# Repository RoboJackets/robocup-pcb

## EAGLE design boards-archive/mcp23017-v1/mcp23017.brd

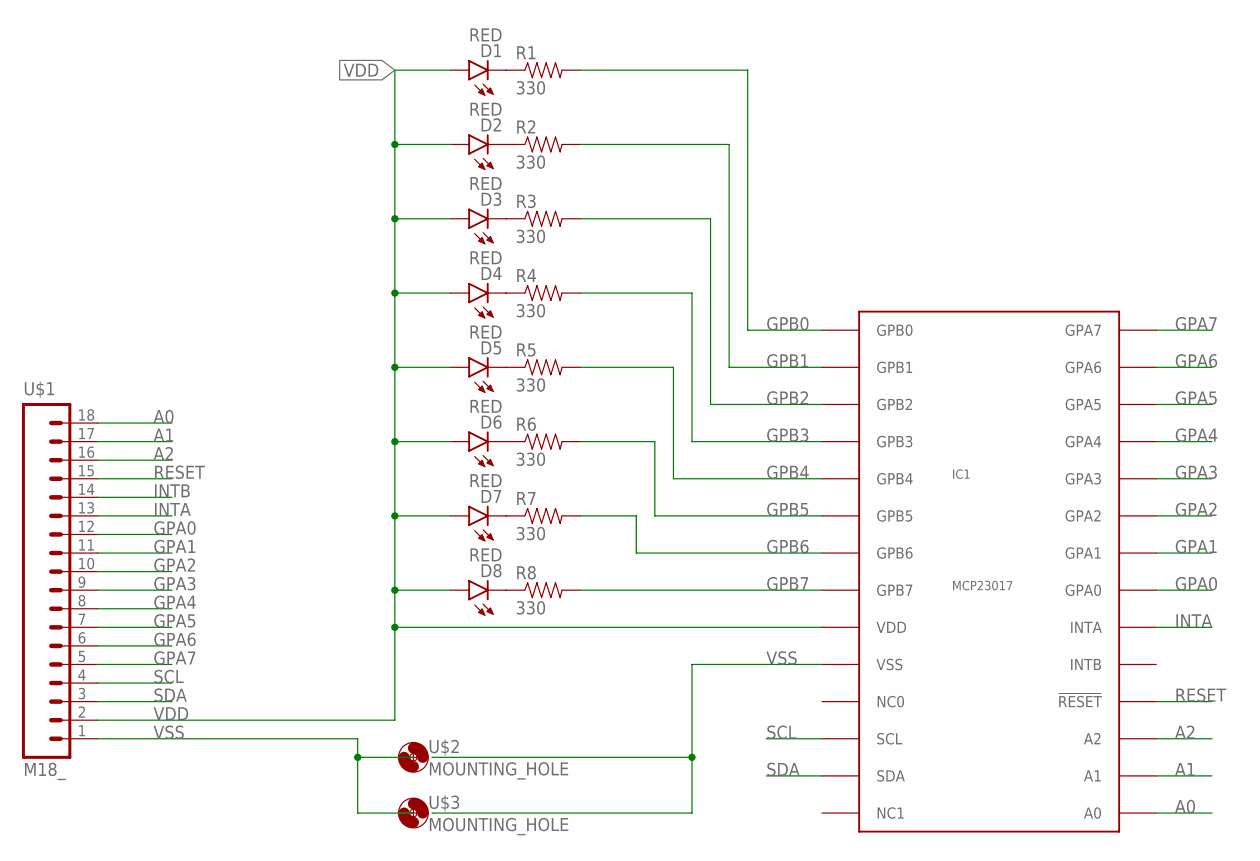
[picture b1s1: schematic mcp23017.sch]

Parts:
D1, D2, D3, D4, D5, D6, D7, D8: RED; LED-0603
IC1: MCP23017; SSOP-28
R1, R2, R3, R4, R5, R6, R7, R8: 330; 0603-RES
U$1: M18_; 1X18
U$2, U$3: MOUNTING_HOLE

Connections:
A0: IC1.15 (A0), U$1.18
A1: IC1.16 (A1), U$1.17
A2: IC1.17 (A2), U$1.16
GPA0: IC1.21 (GPA0), U$1.12
GPA1: IC1.22 (GPA1), U$1.11
GPA2: IC1.23 (GPA2), U$1.10
GPA3: IC1.24 (GPA3), U$1.9
GPA4: IC1.25 (GPA4), U$1.8
GPA5: IC1.26 (GPA5), U$1.7
GPA6: IC1.27 (GPA6), U$1.6
GPA7: IC1.28 (GPA7), U$1.5
GPB0: IC1.1 (GPB0), R1.2
GPB1: IC1.2 (GPB1), R2.2
GPB2: IC1.3 (GPB2), R3.2
GPB3: IC1.4 (GPB3), R4.2
GPB4: IC1.5 (GPB4), R5.2
GPB5: IC1.6 (GPB5), R6.2
GPB6: IC1.7 (GPB6), R7.2
GPB7: IC1.8 (GPB7), R8.2
INTA: IC1.20 (INTA), U$1.13
INTB: U$1.14
unnamed: D1.C, R1.1
unnamed: D2.C, R2.1
unnamed: D3.C, R3.1
unnamed: D4.C, R4.1
unnamed: D5.C, R5.1
unnamed: D6.C, R6.1
unnamed: D7.C, R7.1
unnamed: D8.C, R8.1
RESET: IC1.18 (!RESET!), U$1.15
SCL: IC1.12 (SCL), U$1.4
SDA: IC1.13 (SDA), U$1.3
VDD: D1.A, D2.A, D3.A, D4.A, D5.A, D6.A, D7.A, D8.A, IC1.9 (VDD), U$1.2
VSS: IC1.10 (VSS), U$1.1, U$2.GND, U$3.GND

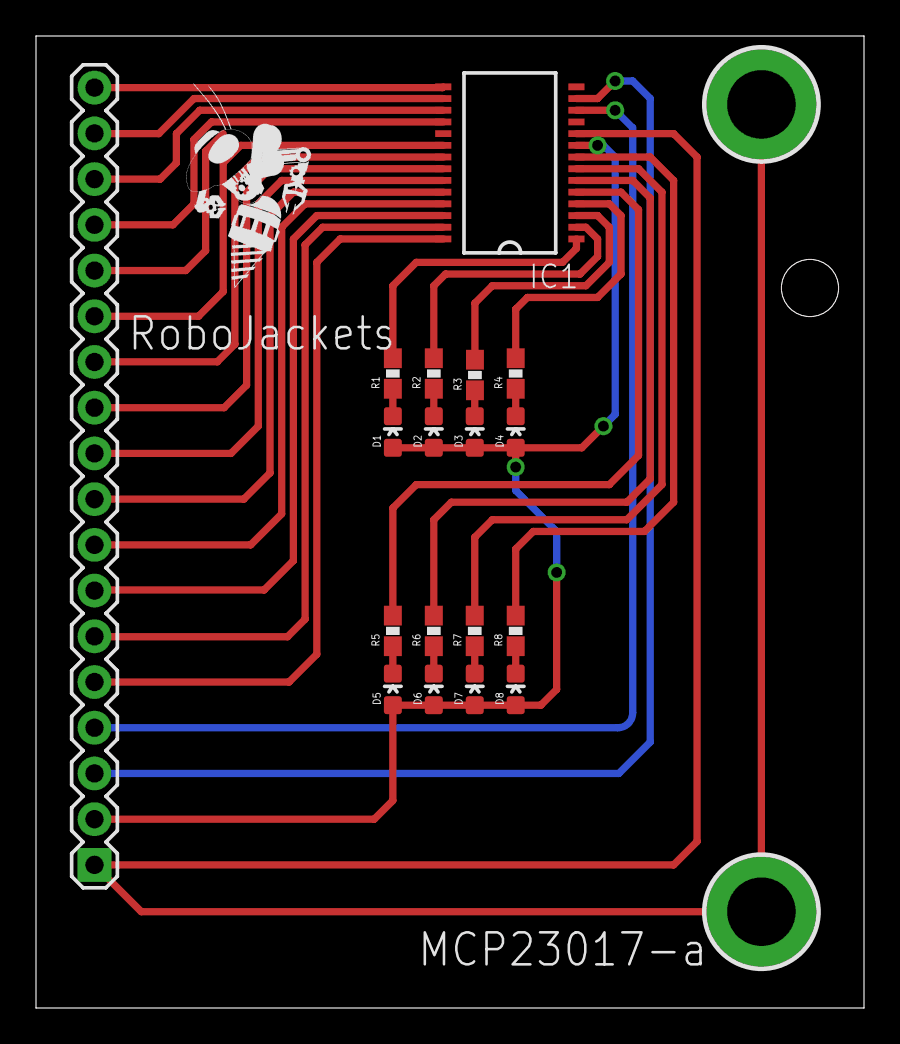
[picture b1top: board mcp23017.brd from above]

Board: 2 copper layers, 46.0 x 54.0 mm, 21 parts (0 on the bottom side), 33 nets.

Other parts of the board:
U$4: ROBOBUZZ_0.6X

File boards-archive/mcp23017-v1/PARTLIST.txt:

Partlist

Exported from mcp23017-v1.brd at 12/27/2014 11:06:29 PM

EAGLE Version 6.5.0 Copyright (c) 1988-2013 CadSoft

Assembly variant: 

Part     Value          Package       Library             Position (mm)         Orientation

D1       RED            LED-0603      SparkFun-LED        (19.825 32)           R0
D2       RED            LED-0603      SparkFun-LED        (22.1 32)             R0
D3       RED            LED-0603      SparkFun-LED        (24.375 32)           R0
D4       RED            LED-0603      SparkFun-LED        (26.65 32)            R0
D5       RED            LED-0603      SparkFun-LED        (19.825 17.7)         R0
D6       RED            LED-0603      SparkFun-LED        (22.1 17.7)           R0
D7       RED            LED-0603      SparkFun-LED        (24.375 17.7)         R0
D8       RED            LED-0603      SparkFun-LED        (26.65 17.7)          R0
IC1      MCP23017       SSOP-28       RoboJackets-ICs     (26.325 46.95)        R180
R1       330            0603-RES      SparkFun-Resistors  (19.825 35.25)        R90
R2       330            0603-RES      SparkFun-Resistors  (22.1 35.25)          R90
R3       330            0603-RES      SparkFun-Resistors  (24.385 35.165)       R90
R4       330            0603-RES      SparkFun-Resistors  (26.65 35.25)         R90
R5       330            0603-RES      SparkFun-Resistors  (19.825 20.95)        R90
R6       330            0603-RES      SparkFun-Resistors  (22.1 20.95)          R90
R7       330            0603-RES      SparkFun-Resistors  (24.375 20.95)        R90
R8       330            0603-RES      SparkFun-Resistors  (26.65 20.95)         R90
U$1      M18_           1X18          SparkFun-Connectors (3.25 7.95)           R90
U$2      MOUNTING_HOLE  MOUNTING_HOLE RoboJackets-Passive (40.3 5.35)           R0
U$3      MOUNTING_HOLE  MOUNTING_HOLE RoboJackets-Passive (40.3 50.2)           R0

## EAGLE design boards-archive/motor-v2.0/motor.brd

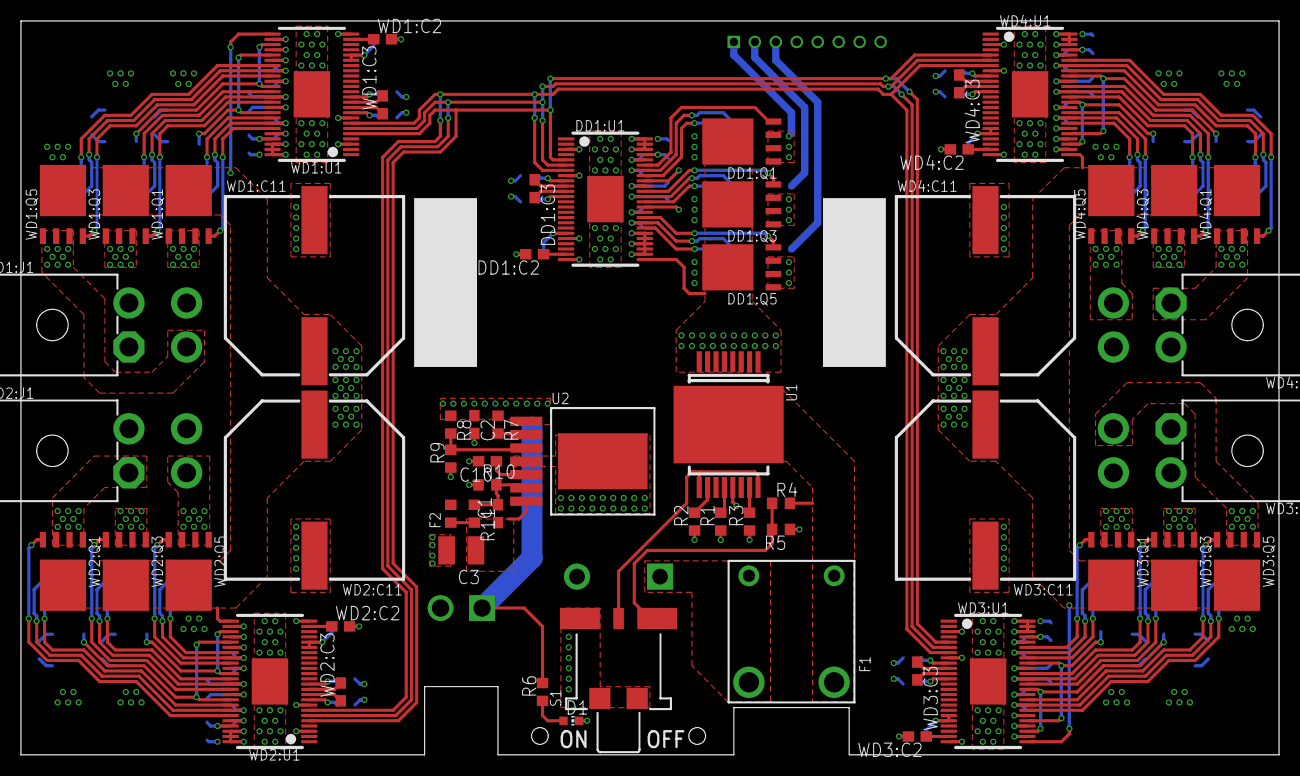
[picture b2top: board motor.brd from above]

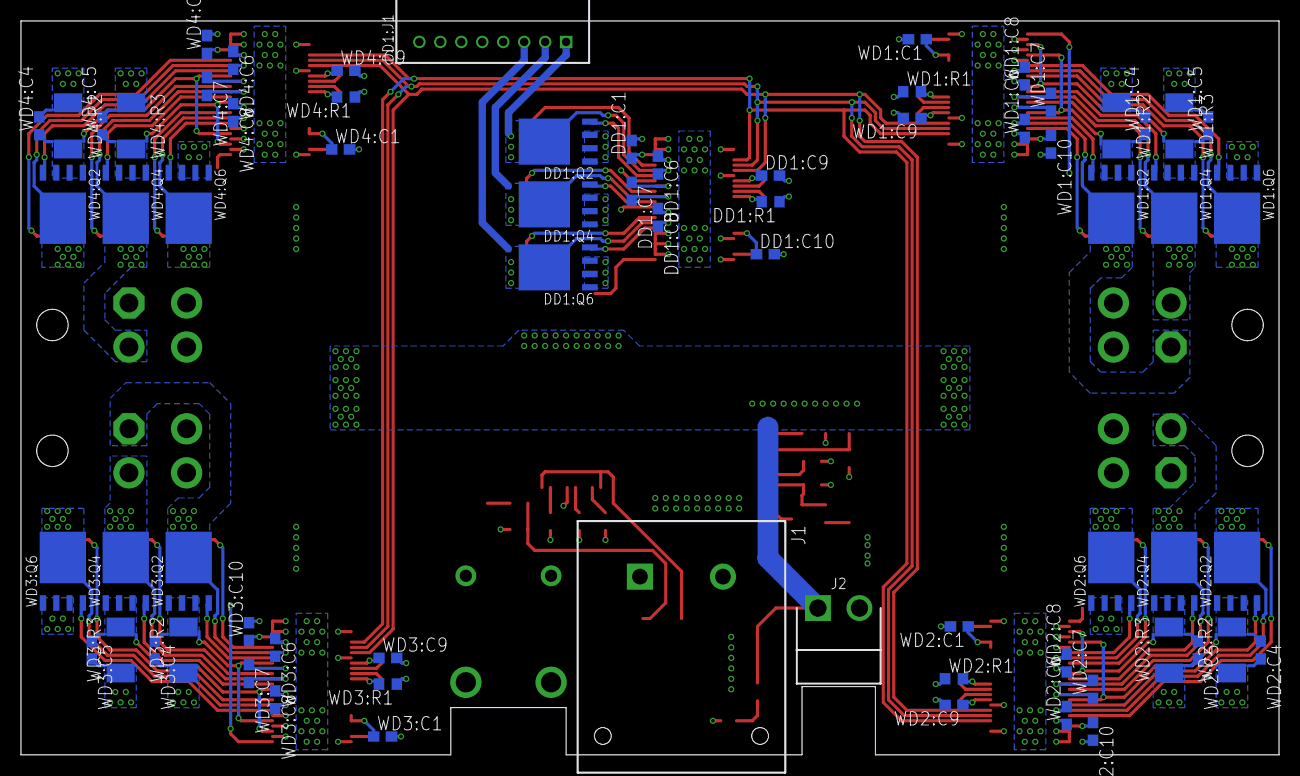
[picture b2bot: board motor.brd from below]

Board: 4 copper layers, 120.0 x 70.0 mm, 128 parts (69 on the bottom side), 112 nets.

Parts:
C1: 0.022uF; C0603
C2: GRM188R6YA106MA73D; C0603
C3: LMK325ABJ107MM-P; C1210
C10: 0.1uF 50V; C0603
D1: Green; CHIP-LED0603
DD1:C1, DD1:C2: 1uF; C0603
DD1:C3: 22000pF 50V; C0603
DD1:C6, DD1:C7, DD1:C8, DD1:C10: 0.1uF 50V; C0603
DD1:C9: 2.2uF 50V; C0603
DD1:J1: 8-PIN_2MM-H; 2MM-8-H
DD1:Q1, DD1:Q2, DD1:Q3, DD1:Q4, DD1:Q5, DD1:Q6: IRFH7545; PQFN_5X6_E
DD1:R1: 10k; R0603
DD1:U1: DRV8303DCA; TSSOP-48_PAD
F1: 30A; FUSEHOLDER_3549_X2
F2: 0603L075SLYR; F0603
J1: DF22-2; DF22-2-H
J2: B2PS-CENTERED-VH(LF)(SN); B2PS-CENTERED
R1: 10k; R0603
R2, R3, R6: 1k; R0603
R4, R8: 270k; R0603
R5, R7, R9: 100k; R0603
R10: 6.49k; R0603
R11: 34k; R0603
S1: 34EWMSP12MRT; 34EWMSP12M6RT
U1: VND5E006ASPTR-E; POWERSO-16
U2: LMZ14201; TO-PMOD-7
WD1:C1, WD1:C2, WD2:C1, WD2:C2, WD3:C1, WD3:C2, WD4:C1, WD4:C2: 1uF; C0603
WD1:C3, WD2:C3, WD3:C3, WD4:C3: 22000pF 50V; C0603
WD1:C4, WD1:C5, WD2:C4, WD2:C5, WD3:C4, WD3:C5, WD4:C4, WD4:C5: 10000pF 50V; C0603
WD1:C6, WD1:C7, WD1:C8, WD1:C10, WD2:C6, WD2:C7, WD2:C8, WD2:C10, WD3:C6, WD3:C7, WD3:C8, WD3:C10, WD4:C6, WD4:C7, WD4:C8, WD4:C10: 0.1uF 50V; C0603
WD1:C9, WD2:C9, WD3:C9, WD4:C9: 2.2uF 50V; C0603
WD1:C11, WD2:C11, WD3:C11, WD4:C11: EEE-FK1H102AM; PANASONIC_J16
WD1:J1, WD2:J1, WD3:J1, WD4:J1: MINIFITJR_HDR_2X2; 0039301040
WD1:Q1, WD1:Q2, WD1:Q3, WD1:Q4, WD1:Q5, WD1:Q6, WD2:Q1, WD2:Q2, WD2:Q3, WD2:Q4, WD2:Q5, WD2:Q6, WD3:Q1, WD3:Q2, WD3:Q3, WD3:Q4, WD3:Q5, WD3:Q6, WD4:Q1, WD4:Q2, WD4:Q3, WD4:Q4, WD4:Q5, WD4:Q6: IRFH7545; PQFN_5X6_E
WD1:R1, WD2:R1, WD3:R1, WD4:R1: 10k; R0603
WD1:R2, WD1:R3, WD2:R2, WD2:R3, WD3:R2, WD3:R3, WD4:R2, WD4:R3: ERJ-MB1SF1M0U; R2010
WD1:U1, WD2:U1, WD3:U1, WD4:U1: DRV8303DCA; TSSOP-48_PAD

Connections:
+3.3V: DD1:C1.1, DD1:C10.1, DD1:J1.7, DD1:R1.1, DD1:U1.19, DD1:U1.45, WD1:C1.1, WD1:C10.1, WD1:R1.1, WD1:U1.19, WD1:U1.20, WD1:U1.45, WD2:C1.1, WD2:C10.1, WD2:R1.1, WD2:U1.19, WD2:U1.20, WD2:U1.45, WD3:C1.1, WD3:C10.1, WD3:R1.1, WD3:U1.19, WD3:U1.20, WD3:U1.45, WD4:C1.1, WD4:C10.1, WD4:R1.1, WD4:U1.19, WD4:U1.20, WD4:U1.45
+18.5V: C2.1, DD1:Q1.5678, DD1:Q3.5678, DD1:Q5.5678, DD1:U1.25, J2.1, R6.2, R7.1, R8.1, U1.1, U1.2, U1.3, U1.4, U1.5, U1.6, U1.7, U1.8, U2.1, WD1:C11.+, WD1:Q1.5678, WD1:Q3.5678, WD1:Q5.5678, WD1:U1.25, WD2:C11.+, WD2:Q1.5678, WD2:Q3.5678, WD2:Q5.5678, WD2:U1.25, WD3:C11.+, WD3:Q1.5678, WD3:Q3.5678, WD3:Q5.5678, WD3:U1.25, WD4:C11.+, WD4:Q1.5678, WD4:Q3.5678, WD4:Q5.5678, WD4:U1.25
DD1:N$1: DD1:C2.1, DD1:U1.23
DD1:N$2: DD1:C3.1, DD1:U1.10
DD1:N$3: DD1:C3.2, DD1:U1.11
DD1:N$4: DD1:C9.1, DD1:U1.9
DD1:N$6: DD1:Q2.4, DD1:U1.41
DD1:N$8: DD1:Q1.4, DD1:U1.43
DD1:N$10: DD1:Q4.4, DD1:U1.36
DD1:N$12: DD1:Q3.4, DD1:U1.38
DD1:N$13: DD1:C6.1, DD1:U1.44
DD1:N$14: DD1:C7.1, DD1:U1.39
DD1:N$16: DD1:Q6.4, DD1:U1.31
DD1:N$17: DD1:Q5.4, DD1:U1.33
DD1:N$18: DD1:C8.1, DD1:U1.34
DD1:N$19: DD1:R1.2, DD1:U1.12
DD1:PHASE_A: DD1:C6.2, DD1:J1.1, DD1:Q1.1, DD1:Q1.2, DD1:Q1.3, DD1:Q2.5678, DD1:U1.42
DD1:PHASE_B: DD1:C7.2, DD1:J1.2, DD1:Q3.1, DD1:Q3.2, DD1:Q3.3, DD1:Q4.5678, DD1:U1.37
DD1:PHASE_C: DD1:C8.2, DD1:J1.3, DD1:Q5.1, DD1:Q5.2, DD1:Q5.3, DD1:Q6.5678, DD1:U1.32
GND: C2.2, C3.2, C10.2, D1.C, DD1:C1.2, DD1:C2.2, DD1:C9.2, DD1:C10.2, DD1:J1.8, DD1:Q2.1, DD1:Q2.2, DD1:Q2.3, DD1:Q4.1, DD1:Q4.2, DD1:Q4.3, DD1:Q6.1, DD1:Q6.2, DD1:Q6.3, DD1:U1.3, DD1:U1.8, DD1:U1.20, DD1:U1.24, DD1:U1.26, DD1:U1.27, DD1:U1.28, DD1:U1.29, DD1:U1.30, DD1:U1.35, DD1:U1.40, DD1:U1.46, DD1:U1.47, DD1:U1.48, DD1:U1.PAD, J1.2, J2.2, R1.1, R2.1, R3.1, R5.1, R9.1, R10.1, S1.3, S1.LEG1, S1.LEG3, U1.13, U2.4, U2.PAD, WD1:C1.2, WD1:C2.2, WD1:C4.2, WD1:C5.2, WD1:C9.2, WD1:C10.2, WD1:C11.-, WD1:Q6.1, WD1:Q6.2, WD1:Q6.3, WD1:R2.1, WD1:R3.1, WD1:U1.3, WD1:U1.8, WD1:U1.24, WD1:U1.26, WD1:U1.28, WD1:U1.30, WD1:U1.46, WD1:U1.47, WD1:U1.48, WD1:U1.PAD, WD2:C1.2, WD2:C2.2, WD2:C4.2, WD2:C5.2, WD2:C9.2, WD2:C10.2, WD2:C11.-, WD2:Q6.1, WD2:Q6.2, WD2:Q6.3, WD2:R2.1, WD2:R3.1, WD2:U1.3, WD2:U1.8, WD2:U1.24, WD2:U1.26, WD2:U1.28, WD2:U1.30, WD2:U1.46, WD2:U1.47, WD2:U1.48, WD2:U1.PAD, WD3:C1.2, WD3:C2.2, WD3:C4.2, WD3:C5.2, WD3:C9.2, WD3:C10.2, WD3:C11.-, WD3:Q6.1, WD3:Q6.2, WD3:Q6.3, WD3:R2.1, WD3:R3.1, WD3:U1.3, WD3:U1.8, WD3:U1.24, WD3:U1.26, WD3:U1.28, WD3:U1.30, WD3:U1.46, WD3:U1.47, WD3:U1.48, WD3:U1.PAD, WD4:C1.2, WD4:C2.2, WD4:C4.2, WD4:C5.2, WD4:C9.2, WD4:C10.2, WD4:C11.-, WD4:Q6.1, WD4:Q6.2, WD4:Q6.3, WD4:R2.1, WD4:R3.1, WD4:U1.3, WD4:U1.8, WD4:U1.24, WD4:U1.26, WD4:U1.28, WD4:U1.30, WD4:U1.46, WD4:U1.47, WD4:U1.48, WD4:U1.PAD
MISO: DD1:U1.6, WD1:U1.6, WD2:U1.6, WD3:U1.6, WD4:U1.6
MOSI: DD1:U1.5, WD1:U1.5, WD2:U1.5, WD3:U1.5, WD4:U1.5
unnamed: R3.2, U1.15
unnamed: R2.2, U1.10
unnamed: R1.2, U1.12
unnamed: R4.1, R5.2, S1.1
unnamed: S1.2, U1.9, U1.16
unnamed: D1.A, R6.1
unnamed: C10.1, U2.5
unnamed: R7.2, U2.2
unnamed: R8.2, R9.2, U2.3
unnamed: C1.2, R10.2, R11.1, U2.6
unnamed: C1.1, C3.1, F2.1, R11.2, U2.7
SCK: DD1:U1.7, WD1:U1.7, WD2:U1.7, WD3:U1.7, WD4:U1.7
VBATT: F1.2, F1.LEG2, R4.2, U1.17
VIN: F1.1, F1.LEG1, J1.1
WD1:N$1: WD1:C2.1, WD1:U1.23
WD1:N$2: WD1:C3.1, WD1:U1.10
WD1:N$3: WD1:C3.2, WD1:U1.11
WD1:N$4: WD1:C9.1, WD1:U1.9
WD1:N$6: WD1:Q2.4, WD1:U1.41
WD1:N$8: WD1:Q1.4, WD1:U1.43
WD1:N$10: WD1:Q4.4, WD1:U1.36
WD1:N$12: WD1:Q3.4, WD1:U1.38
WD1:N$13: WD1:C6.1, WD1:U1.44
WD1:N$14: WD1:C7.1, WD1:U1.39
WD1:N$16: WD1:Q6.4, WD1:U1.31
WD1:N$17: WD1:Q5.4, WD1:U1.33
WD1:N$18: WD1:C8.1, WD1:U1.34
WD1:N$19: WD1:R1.2, WD1:U1.12
WD1:PHASE_A: WD1:C6.2, WD1:J1.1, WD1:Q1.1, WD1:Q1.2, WD1:Q1.3, WD1:Q2.5678, WD1:U1.42
WD1:PHASE_B: WD1:C7.2, WD1:J1.2, WD1:Q3.1, WD1:Q3.2, WD1:Q3.3, WD1:Q4.5678, WD1:U1.37
WD1:PHASE_C: WD1:C8.2, WD1:J1.3, WD1:Q5.1, WD1:Q5.2, WD1:Q5.3, WD1:Q6.5678, WD1:U1.32
WD1:S1: WD1:C4.1, WD1:Q2.1, WD1:Q2.2, WD1:Q2.3, WD1:R2.2, WD1:U1.29, WD1:U1.40
WD1:S2: WD1:C5.1, WD1:Q4.1, WD1:Q4.2, WD1:Q4.3, WD1:R3.2, WD1:U1.27, WD1:U1.35
WD2:N$1: WD2:C2.1, WD2:U1.23
WD2:N$2: WD2:C3.1, WD2:U1.10
WD2:N$3: WD2:C3.2, WD2:U1.11
WD2:N$4: WD2:C9.1, WD2:U1.9
WD2:N$6: WD2:Q2.4, WD2:U1.41
WD2:N$8: WD2:Q1.4, WD2:U1.43
WD2:N$10: WD2:Q4.4, WD2:U1.36
WD2:N$12: WD2:Q3.4, WD2:U1.38
WD2:N$13: WD2:C6.1, WD2:U1.44
WD2:N$14: WD2:C7.1, WD2:U1.39
WD2:N$16: WD2:Q6.4, WD2:U1.31
WD2:N$17: WD2:Q5.4, WD2:U1.33
WD2:N$18: WD2:C8.1, WD2:U1.34
WD2:N$19: WD2:R1.2, WD2:U1.12
WD2:PHASE_A: WD2:C6.2, WD2:J1.1, WD2:Q1.1, WD2:Q1.2, WD2:Q1.3, WD2:Q2.5678, WD2:U1.42
WD2:PHASE_B: WD2:C7.2, WD2:J1.2, WD2:Q3.1, WD2:Q3.2, WD2:Q3.3, WD2:Q4.5678, WD2:U1.37
WD2:PHASE_C: WD2:C8.2, WD2:J1.3, WD2:Q5.1, WD2:Q5.2, WD2:Q5.3, WD2:Q6.5678, WD2:U1.32
WD2:S1: WD2:C4.1, WD2:Q2.1, WD2:Q2.2, WD2:Q2.3, WD2:R2.2, WD2:U1.29, WD2:U1.40
WD2:S2: WD2:C5.1, WD2:Q4.1, WD2:Q4.2, WD2:Q4.3, WD2:R3.2, WD2:U1.27, WD2:U1.35
WD3:N$1: WD3:C2.1, WD3:U1.23
WD3:N$2: WD3:C3.1, WD3:U1.10
WD3:N$3: WD3:C3.2, WD3:U1.11
WD3:N$4: WD3:C9.1, WD3:U1.9
WD3:N$6: WD3:Q2.4, WD3:U1.41
WD3:N$8: WD3:Q1.4, WD3:U1.43
WD3:N$10: WD3:Q4.4, WD3:U1.36
WD3:N$12: WD3:Q3.4, WD3:U1.38
WD3:N$13: WD3:C6.1, WD3:U1.44
WD3:N$14: WD3:C7.1, WD3:U1.39
WD3:N$16: WD3:Q6.4, WD3:U1.31
WD3:N$17: WD3:Q5.4, WD3:U1.33
WD3:N$18: WD3:C8.1, WD3:U1.34
WD3:N$19: WD3:R1.2, WD3:U1.12
WD3:PHASE_A: WD3:C6.2, WD3:J1.1, WD3:Q1.1, WD3:Q1.2, WD3:Q1.3, WD3:Q2.5678, WD3:U1.42
WD3:PHASE_B: WD3:C7.2, WD3:J1.2, WD3:Q3.1, WD3:Q3.2, WD3:Q3.3, WD3:Q4.5678, WD3:U1.37
WD3:PHASE_C: WD3:C8.2, WD3:J1.3, WD3:Q5.1, WD3:Q5.2, WD3:Q5.3, WD3:Q6.5678, WD3:U1.32
WD3:S1: WD3:C4.1, WD3:Q2.1, WD3:Q2.2, WD3:Q2.3, WD3:R2.2, WD3:U1.29, WD3:U1.40
WD3:S2: WD3:C5.1, WD3:Q4.1, WD3:Q4.2, WD3:Q4.3, WD3:R3.2, WD3:U1.27, WD3:U1.35
WD4:N$1: WD4:C2.1, WD4:U1.23
WD4:N$2: WD4:C3.1, WD4:U1.10
WD4:N$3: WD4:C3.2, WD4:U1.11
WD4:N$4: WD4:C9.1, WD4:U1.9
WD4:N$6: WD4:Q2.4, WD4:U1.41
WD4:N$8: WD4:Q1.4, WD4:U1.43
WD4:N$10: WD4:Q4.4, WD4:U1.36
WD4:N$12: WD4:Q3.4, WD4:U1.38
WD4:N$13: WD4:C6.1, WD4:U1.44
WD4:N$14: WD4:C7.1, WD4:U1.39
WD4:N$16: WD4:Q6.4, WD4:U1.31
WD4:N$17: WD4:Q5.4, WD4:U1.33
WD4:N$18: WD4:C8.1, WD4:U1.34
WD4:N$19: WD4:R1.2, WD4:U1.12
WD4:PHASE_A: WD4:C6.2, WD4:J1.1, WD4:Q1.1, WD4:Q1.2, WD4:Q1.3, WD4:Q2.5678, WD4:U1.42
WD4:PHASE_B: WD4:C7.2, WD4:J1.2, WD4:Q3.1, WD4:Q3.2, WD4:Q3.3, WD4:Q4.5678, WD4:U1.37
WD4:PHASE_C: WD4:C8.2, WD4:J1.3, WD4:Q5.1, WD4:Q5.2, WD4:Q5.3, WD4:Q6.5678, WD4:U1.32
WD4:S1: WD4:C4.1, WD4:Q2.1, WD4:Q2.2, WD4:Q2.3, WD4:R2.2, WD4:U1.29, WD4:U1.40
WD4:S2: WD4:C5.1, WD4:Q4.1, WD4:Q4.2, WD4:Q4.3, WD4:R3.2, WD4:U1.27, WD4:U1.35

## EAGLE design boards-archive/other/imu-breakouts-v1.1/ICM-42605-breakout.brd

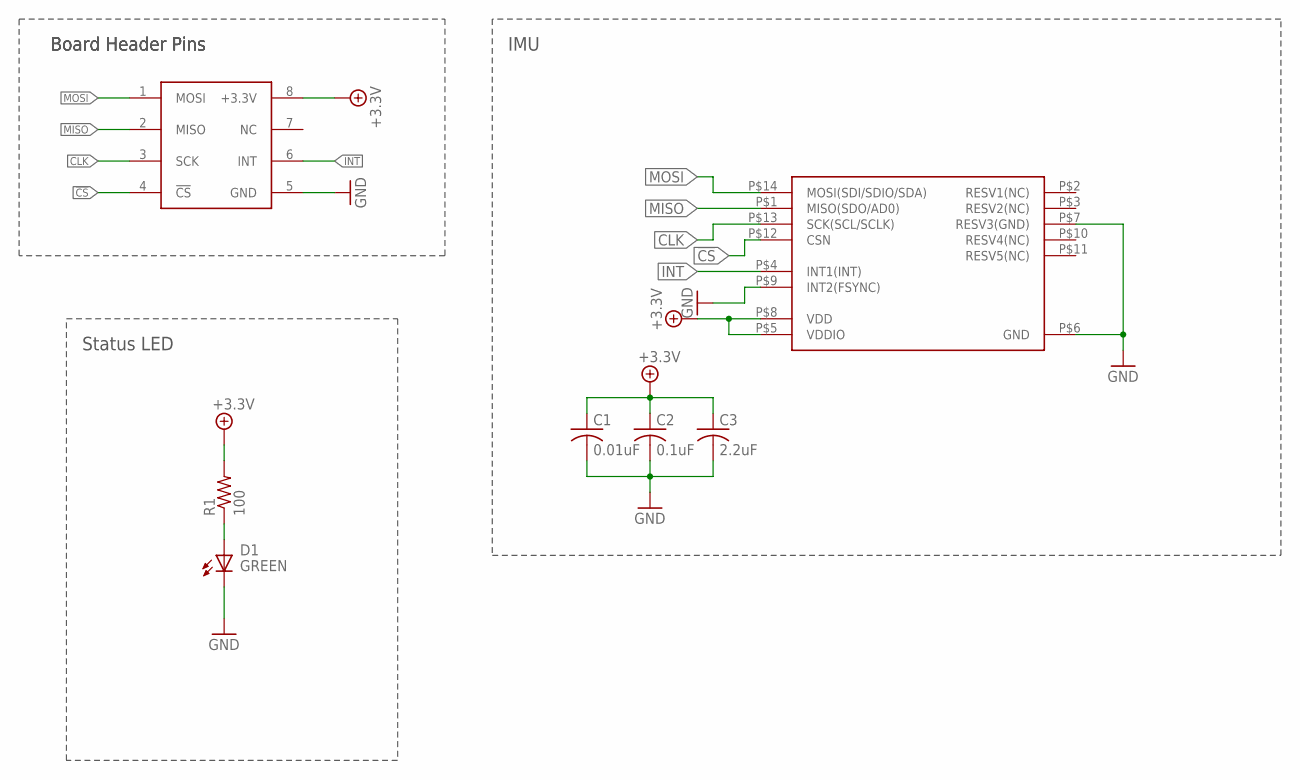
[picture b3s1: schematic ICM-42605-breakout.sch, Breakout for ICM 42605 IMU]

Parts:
C1: 0.01uF; C0603
C2: 0.1uF; C0603
C3: 2.2uF; C0603
D1: GREEN; CHIP-LED0603
KIT1: IMUIMU-KIT; IMU-KIT
R1: 100; R0603W
U3: ICM-42605; ICM-442605-2530091

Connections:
!CS!: KIT1.4 (!CS!), U3.P$12 (CSN)
+3.3V: C1.1, C2.1, C3.1, KIT1.8 (+3.3V), R1.2 (PIN2), U3.P$5 (VDDIO), U3.P$8 (VDD)
CLK: KIT1.3 (SCK), U3.P$13 (SCK(SCL/SCLK))
GND: C1.2, C2.2, C3.2, D1.C (K), KIT1.5 (GND), U3.P$6 (GND), U3.P$7 (RESV3(GND)), U3.P$9 (INT2(FSYNC))
INT: KIT1.6 (INT), U3.P$4 (INT1(INT))
MISO: KIT1.2 (MISO), U3.P$1 (MISO(SDO/AD0))
MOSI: KIT1.1 (MOSI), U3.P$14 (MOSI(SDI/SDIO/SDA))
unnamed: D1.A, R1.1 (PIN1)

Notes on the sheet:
IMU
Board Header Pins
Status LED

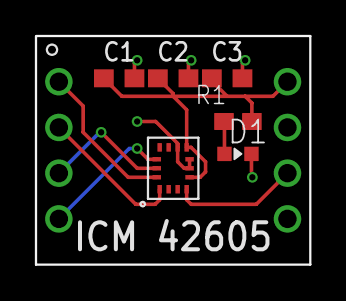
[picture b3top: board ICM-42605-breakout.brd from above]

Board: 2 copper layers, 15.2 x 12.7 mm, 7 parts (0 on the bottom side), 8 nets.

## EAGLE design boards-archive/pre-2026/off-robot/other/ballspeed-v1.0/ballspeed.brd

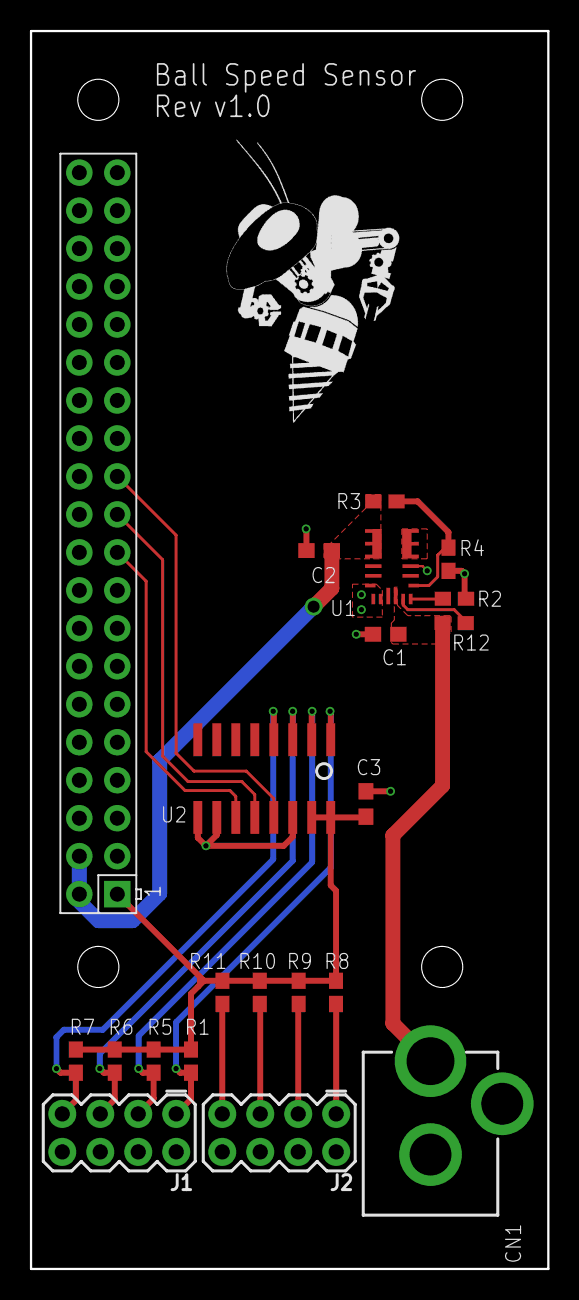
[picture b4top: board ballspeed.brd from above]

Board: 2 copper layers, 34.6 x 82.8 mm, 22 parts (0 on the bottom side), 18 nets.

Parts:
C1: 10uF; C0603
C2: 22uF; C0603
C3: .1uF; C0603
CN1: DCJACK_2MM_PTH
J1, J2: 2X4
R1, R5, R6, R7: 10k; R0603W
R2: 63.4k; R0603W
R3: 160k; R0603W
R4: 30.1k; R0603W
R8, R9, R10, R11: 100; R0603W
R12: 100k; R0603W
U1: MPM3620GQV-P
U2: MCP3008SL; SOIC-16
U$1: ROBOBUZZ_1.0X
U$2: RPI-ZERO; RASPBERRYPI_BASTELSTUBE_V13_RASPI_BOARD_B+_FULL

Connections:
+3.3V: C3.1, R1.1, R5.1, R6.1, R7.1, R8.1, R9.1, R10.1, R11.1, U2.15, U2.16, U$2.1
+5V: C2.1, R3.2, U1.789, U$2.2, U$2.4
+12V: C1.1, CN1.PWR, R12.2, U1.16
CLK: U2.13, U$2.23
GND: C1.2, C2.2, C3.2, CN1.GND, J1.2, J1.4, J1.6, J1.8, J2.2, J2.4, J2.6, J2.8, R2.1, R4.1, U1.3, U1.12, U1.13, U1.14, U2.9, U2.10, U2.14, U$2.6, U$2.9, U$2.14, U$2.20, U$2.25, U$2.30, U$2.34, U$2.39
IR1: J1.1, R1.2, U2.1
IR1-3.3V: J2.1, R8.2
IR2: J1.3, R5.2, U2.2
IR2-3.3V: J2.3, R9.2
IR3: J1.5, R6.2, U2.3
IR3-3.3V: J2.5, R10.2
IR4: J1.7, R7.2, U2.4
IR4-3.3V: J2.7, R11.2
MISO: U2.12, U$2.21
MOSI: U2.11, U$2.19
unnamed: R3.1, R4.2, U1.1
unnamed: R2.2, U1.18
unnamed: R12.1, U1.17

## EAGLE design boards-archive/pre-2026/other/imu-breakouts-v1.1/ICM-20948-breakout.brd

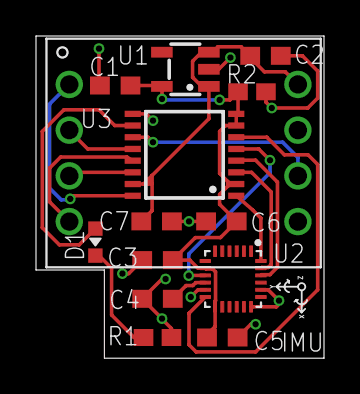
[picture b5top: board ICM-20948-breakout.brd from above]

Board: 2 copper layers, 16.0 x 17.9 mm, 15 parts (1 on the bottom side), 16 nets.

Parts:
C1, C2: 1uF; C0603
C3, C4, C6, C7: 0.1uF; C0603
C5: 1.0uF; C0603
D1: GREEN; CHIP-LED0603
KIT1: IMU
R1: 220; R0603W
R2: 50k; R0603W
U1: NCP161; SOT-23-5
U2: ICM-20948
U3: TXB0106; TSSOP-16
U$1: ROBOBUZZ_0.4X

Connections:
!CS!/1.8V: U2.22, U3.4
!CS!/3.3V: KIT1.4, U3.13
+1.8V: C1.1, C3.1, C5.1, C6.1, R2.1, U1.5, U2.8, U2.13, U3.2, U3.7, U3.8
+1.8V-D1-OUT: D1.C, R1.2
+3.3V: C2.1, C7.1, KIT1.8, U1.1, U1.3, U3.15
CLK/1.8V: U2.23, U3.3
CLK/3.3V: KIT1.3, U3.14
GND: C1.2, C2.2, C3.2, C4.2, C5.2, C6.2, C7.2, KIT1.5, R1.1, R2.2, U1.2, U2.11, U2.18, U2.20, U3.9
INT/1.8V: U2.12, U3.6
INT/3.3V: KIT1.6, U3.11
MISO/1.8V: U2.9, U3.5
MISO/3.3V: KIT1.2, U3.12
MOSI/1.8V: U2.24, U3.1
MOSI/3.3V: KIT1.1, U3.16
PRE-LED-3.3V: D1.A, U3.10
REGOUT: C4.1, U2.10

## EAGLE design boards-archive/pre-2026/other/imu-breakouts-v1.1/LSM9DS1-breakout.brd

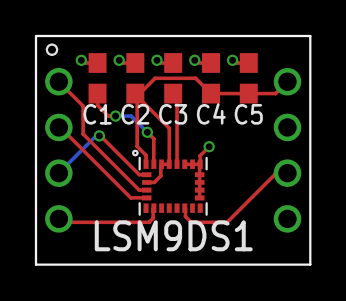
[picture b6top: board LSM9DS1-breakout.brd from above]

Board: 2 copper layers, 15.2 x 12.7 mm, 7 parts (0 on the bottom side), 9 nets.

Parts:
C1, C2: 0.1uF; C0603
C3: 0.01uF 16V; C0603
C4: 1uF; C0603
C5: 10uF; C0603
KIT1: IMUIMU-KIT; IMU-KIT
U1: LSM9DS1; LGA-24L

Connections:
!CS!: KIT1.4, U1.7
+3.3V: C2.1, C4.1, C5.1, KIT1.8, U1.1, U1.3, U1.22, U1.23
C1: C1.1, U1.24
CAP: C3.1, U1.21
CLK: KIT1.3, U1.2
GND: C1.2, C2.2, C3.2, C4.2, C5.2, KIT1.5, U1.14, U1.15, U1.16, U1.17, U1.18, U1.19, U1.20
INT: KIT1.6, U1.11
MISO: KIT1.2, U1.5
MOSI: KIT1.1, U1.4

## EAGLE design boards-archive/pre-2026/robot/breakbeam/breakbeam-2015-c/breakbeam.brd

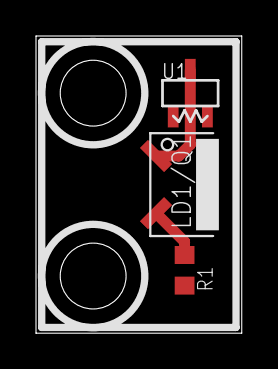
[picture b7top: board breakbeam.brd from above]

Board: 2 copper layers, 11.4 x 16.5 mm, 4 parts (0 on the bottom side), 4 nets.

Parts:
LD1/Q1: 2LEAD_H_FACEDOWN_XSHORT_MIN
R1: R0603
R3: 0.3k-2.2k; GHOST_0.075
U1: SOT-23-3

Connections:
+5V: R3.P$2, U1.2
GND: LD1/Q1.1, U1.3
unnamed: LD1/Q1.2, R1.2
SERIAL_ID: R3.P$1, U1.1

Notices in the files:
parts and their libraries:
SparkFun-Resistors: Licensing: Creative Commons ShareAlike 4.0 International - https://creativecommons.org/licenses/by-sa/4.0
